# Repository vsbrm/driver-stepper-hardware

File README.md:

# Stepper motor driver board
#### Parameters:
* Supply voltage: ?? - ?? V
* Supply max current: ?? A
* Drive current: ?? A

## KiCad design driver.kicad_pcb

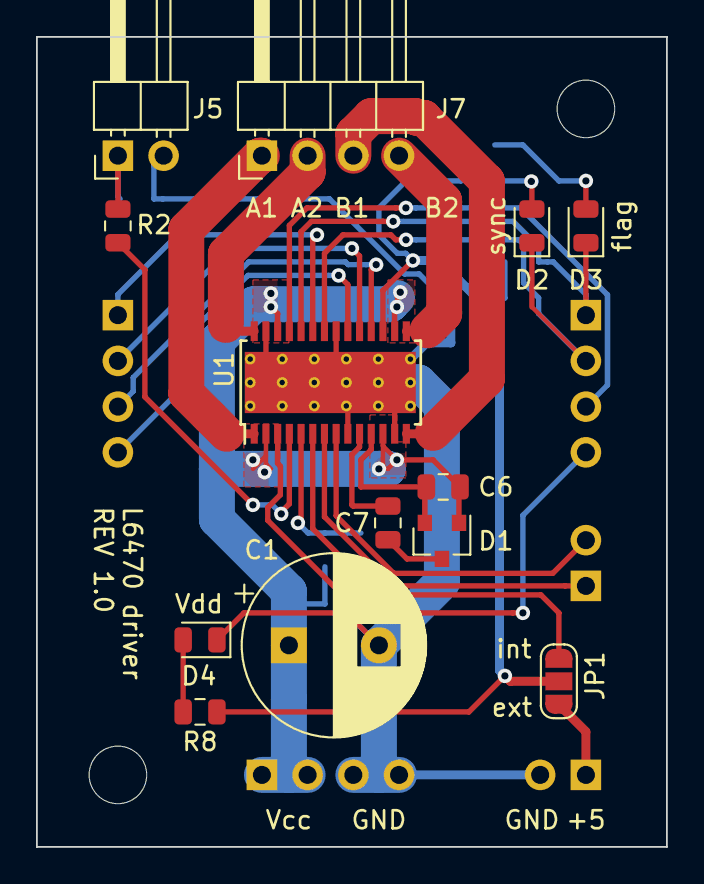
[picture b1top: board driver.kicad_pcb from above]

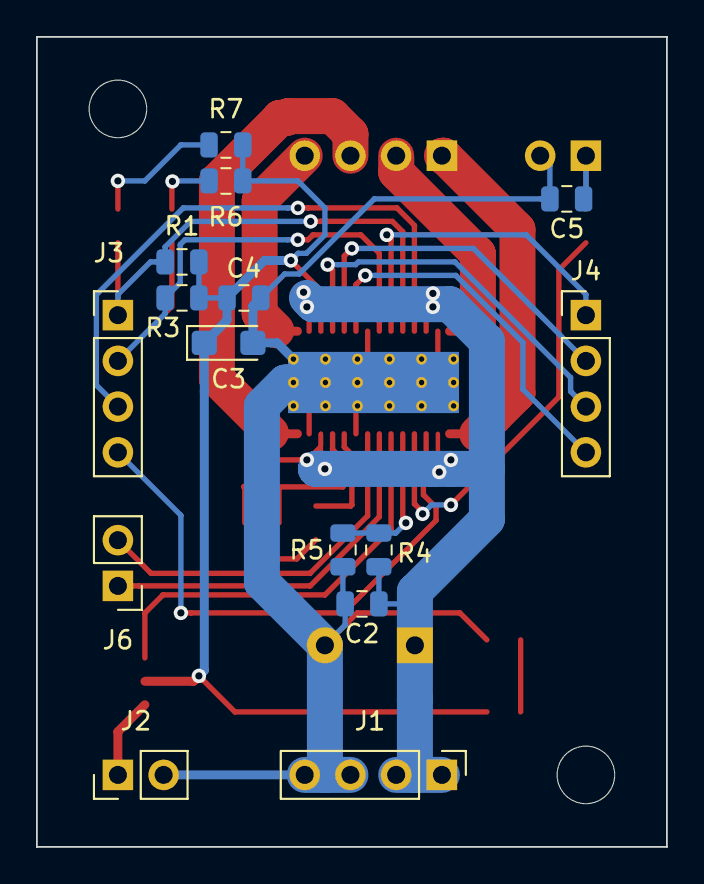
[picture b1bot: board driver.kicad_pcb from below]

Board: 2 copper layers, 35.0 x 45.0 mm, 30 parts (15 on the bottom side), 28 nets.

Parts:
C1: CP; CP_Radial_D10.0mm_P5.00mm
C2, C4, C5, C6, C7: C; C_0805_2012Metric
C3: CP; CP_EIA-3216-18_Kemet-A
D1: BAV99; SOT-23
D2, D3, D4: LED; LED_0805_2012Metric
H1, H2: MountingHole; MountingHole_3.2mm_M3
J1, J3, J4: Conn_01x04; PinHeader_1x04_P2.54mm_Vertical
J2, J6: Conn_01x02; PinHeader_1x02_P2.54mm_Vertical
J5: Conn_01x02; PinHeader_1x02_P2.54mm_Horizontal
J7: Conn_01x04; PinHeader_1x04_P2.54mm_Horizontal
JP1: SolderJumper_3_Open; SolderJumper-3_P1.3mm_Open_RoundedPad1.0x1.5mm_NumberLabels
R1, R2, R3, R4, R5, R6, R7, R8: R; R_0805_2012Metric
U1: L6470H; HTSSOP-28-1EP_4.4x9.7mm_P0.65mm_EP3.4x9.5mm_ThermalVias

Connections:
+5V: J2.1, JP1.3
/~BUSY: D2.1, J3.2, R3.2, U1.22
/~FLAG: D3.1, J3.1, R1.2, U1.24
GND: C1.2, C2.2, C3.2, C4.2, C5.2, D4.1, J1.3, J1.4, J2.2, J5.2, R5.2, U1.9, U1.13, U1.21, U1.27, U1.29
unnamed: C5.1, J5.1, R2.1
unnamed: C6.2, D1.2, U1.11
unnamed: C7.1, D1.3
unnamed: C7.2, U1.10
unnamed: D2.2, R6.2
unnamed: D3.2, R7.2
unnamed: D4.2, R8.2
unnamed: J3.3, U1.25
unnamed: J3.4, U1.3
unnamed: J4.1, U1.23
unnamed: J4.2, U1.19
unnamed: J4.3, U1.18
unnamed: J4.4, U1.20
unnamed: J6.1, U1.7
unnamed: J6.2, U1.8
unnamed: J7.1, U1.1
unnamed: J7.2, U1.28
unnamed: J7.3, U1.14
unnamed: J7.4, U1.15
unnamed: JP1.1, U1.6
unnamed: R2.2, U1.4
unnamed: R4.2, R5.1, U1.5
VCC: C1.1, C2.1, C6.1, D1.1, J1.1, J1.2, R4.1, U1.2, U1.12, U1.16, U1.26
VDD: C3.1, C4.1, JP1.2, R1.1, R3.1, R6.1, R7.1, R8.1, U1.17

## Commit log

2019-08-28 Initial commit.
    * Init readme
    * Create KiCAD project
    * Add .gitignore
2019-11-02 Create schematic
2019-11-10 Update schematic
2019-11-10 Silkscreen
2019-11-11 Assign values
2019-11-26 REV 1.0
2019-11-30 Fix silcscreen
